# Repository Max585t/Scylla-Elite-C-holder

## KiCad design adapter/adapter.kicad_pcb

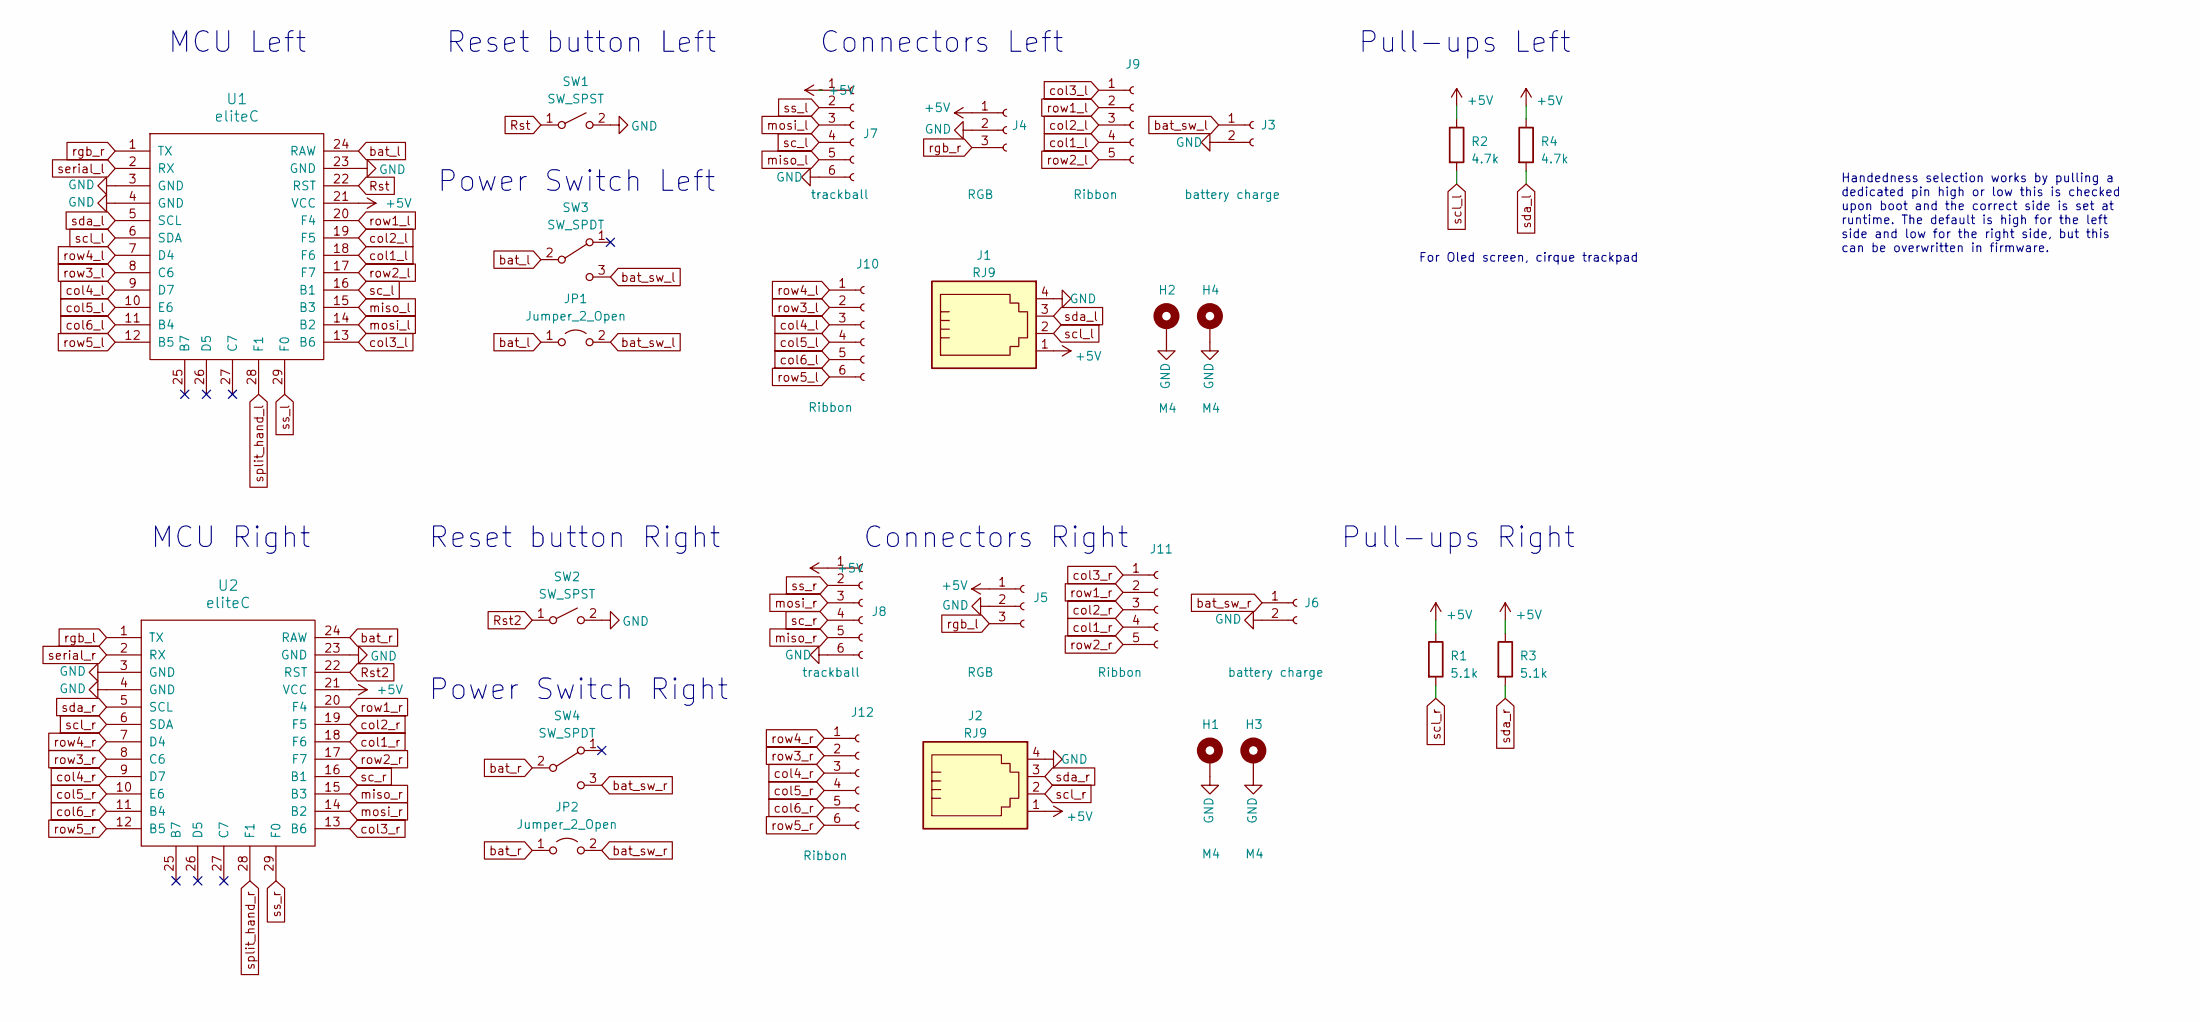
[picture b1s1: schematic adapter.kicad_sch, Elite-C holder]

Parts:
H1, H2, H3, H4: M4; MountingHole_4mm_Pad_thin
J1, J2: RJ9; MOLEX_0955012401
J3, J6: battery charge; PinHeader_1x02_P2.54mm_Vertical
J4, J5: RGB; header1x03
J7, J8: trackball; 6_PinHeader
J9, J11: Ribbon; 5_PinHeader
J10, J12: Ribbon; 6_PinHeader
JP1, JP2: Jumper_2_Open; power_switch_jumper
R1, R3: 5.1k; R_1206_handsolder; JLCPCB BOM 1
R2, R4: 4.7k; R_1206_handsolder; JLCPCB BOM 1
SW1, SW2: SW_SPST; PushSwitch
SW3, SW4: SW_SPDT; SW_SPDT+H-MSK12C01_hor(7pin_SMD)
U1, U2: eliteC; Elite-C

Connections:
+5V: J1.1, J2.1, J4.1, J5.1, J7.1, J8.1, R1.1, R2.1, R3.1, R4.1, U1.21 (VCC), U2.21 (VCC)
GND: H1.1, H2.1, H3.1, H4.1, J1.4, J2.4, J3.2, J4.2, J5.2, J6.2, J7.6, J8.6, SW1.2 (B), SW2.2 (B), U1.3 (GND), U1.4 (GND), U1.23 (GND), U2.3 (GND), U2.4 (GND), U2.23 (GND)
Rst: SW1.1 (A), U1.22 (RST)
Rst2: SW2.1 (A), U2.22 (RST)
bat_l: JP1.1 (A), SW3.2 (B), U1.24 (RAW)
bat_r: JP2.1 (A), SW4.2 (B), U2.24 (RAW)
bat_sw_l: J3.1, JP1.2 (B), SW3.3 (C)
bat_sw_r: J6.1, JP2.2 (B), SW4.3 (C)
col1_l: J9.4, U1.18 (F6)
col1_r: J11.4, U2.18 (F6)
col2_l: J9.3, U1.19 (F5)
col2_r: J11.3, U2.19 (F5)
col3_l: J9.1, U1.13 (B6)
col3_r: J11.1, U2.13 (B6)
col4_l: J10.3, U1.9 (D7)
col4_r: J12.3, U2.9 (D7)
col5_l: J10.4, U1.10 (E6)
col5_r: J12.4, U2.10 (E6)
col6_l: J10.5, U1.11 (B4)
col6_r: J12.5, U2.11 (B4)
miso_l: J7.5, U1.15 (B3)
miso_r: J8.5, U2.15 (B3)
mosi_l: J7.3, U1.14 (B2)
mosi_r: J8.3, U2.14 (B2)
rgb_l: J5.3, U2.1 (TX)
rgb_r: J4.3, U1.1 (TX)
row1_l: J9.2, U1.20 (F4)
row1_r: J11.2, U2.20 (F4)
row2_l: J9.5, U1.17 (F7)
row2_r: J11.5, U2.17 (F7)
row3_l: J10.2, U1.8 (C6)
row3_r: J12.2, U2.8 (C6)
row4_l: J10.1, U1.7 (D4)
row4_r: J12.1, U2.7 (D4)
row5_l: J10.6, U1.12 (B5)
row5_r: J12.6, U2.12 (B5)
sc_l: J7.4, U1.16 (B1)
sc_r: J8.4, U2.16 (B1)
scl_l: J1.2, R2.2, U1.6 (SDA)
scl_r: J2.2, R1.2, U2.6 (SDA)
sda_l: J1.3, R4.2, U1.5 (SCL)
sda_r: J2.3, R3.2, U2.5 (SCL)
serial_l: U1.2 (RX)
serial_r: U2.2 (RX)
split_hand_l: U1.28 (F1)
split_hand_r: U2.28 (F1)
ss_l: J7.2, U1.29 (F0)
ss_r: J8.2, U2.29 (F0)

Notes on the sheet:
Power Switch Right
Reset button Left
For Oled screen, cirque trackpad
Power Switch Left
Connectors Left
Pull-ups Right
Reset button Right
Handedness selection works by pulling a dedicated pin high or low this is checked upon boot and the correct side is set at runtime. The default is high for the left side and low for the right side, but this can be overwritten in firmware.
MCU Left
MCU Right
Pull-ups Left
Connectors Right

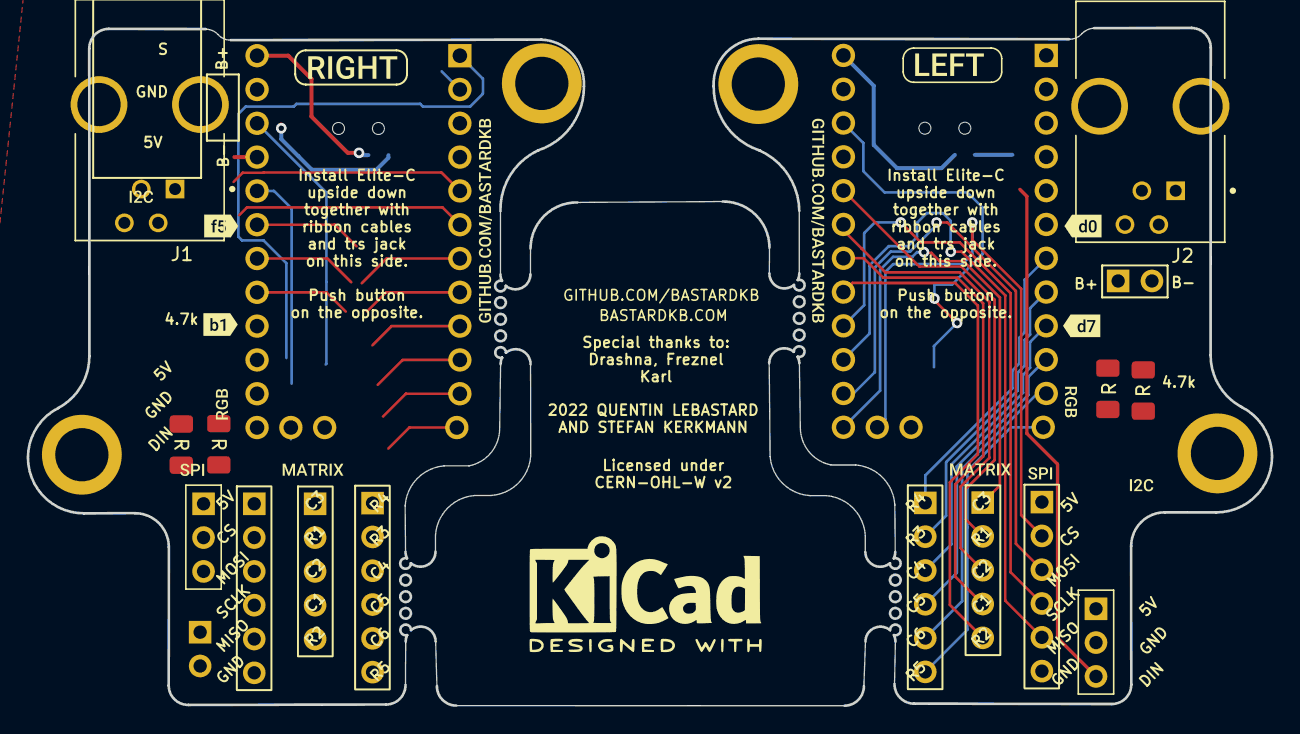
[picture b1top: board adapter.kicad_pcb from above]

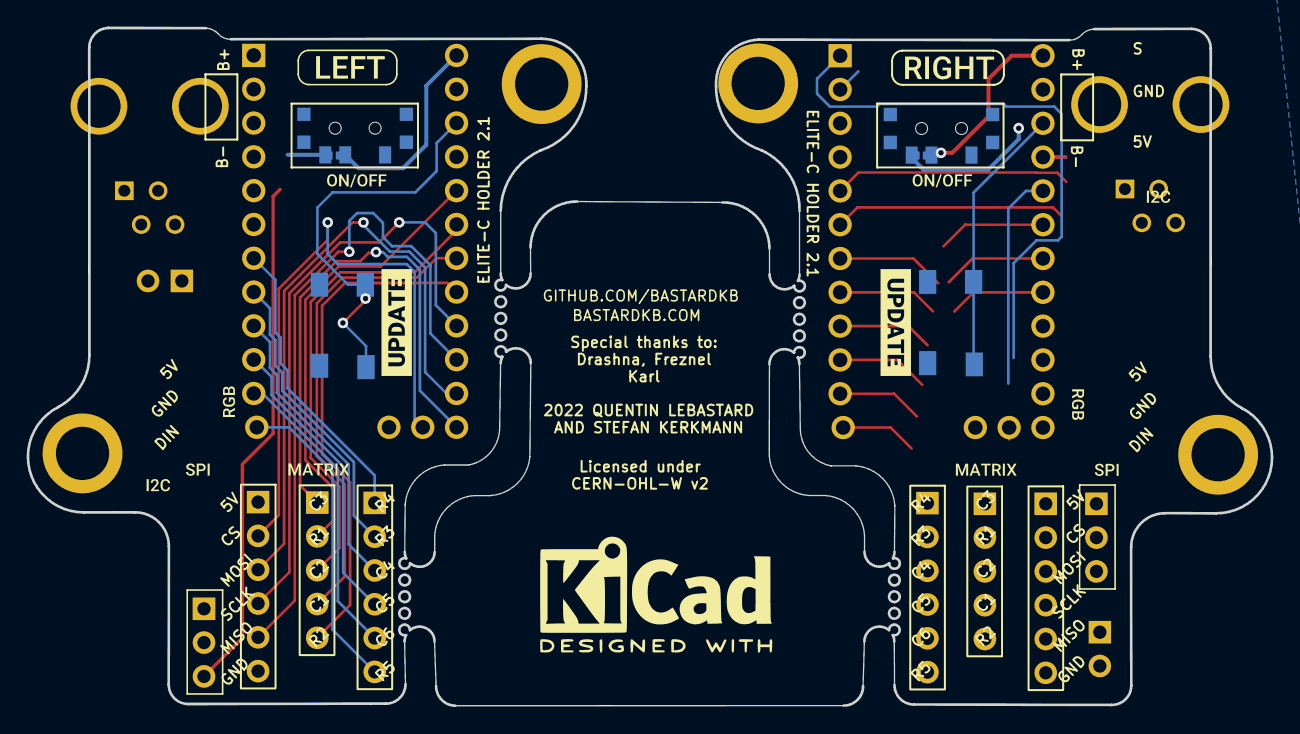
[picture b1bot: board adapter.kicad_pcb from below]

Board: 2 copper layers, 93.5 x 50.9 mm, 58 parts (22 on the bottom side), 44 nets.

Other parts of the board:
kibuzzard-61F01A92, kibuzzard-61F01A92#2: G***; kibuzzard-61F01A92
kibuzzard-61F01B61, kibuzzard-61F01B61#2: G***; kibuzzard-61F01B61
kibuzzard-61F01C84, kibuzzard-61F01C84#2: G***; kibuzzard-61F01C84
kibuzzard-61F019CB, kibuzzard-61F019CB#2, kibuzzard-61F019CB#3, kibuzzard-61F019CB#4: G***; kibuzzard-61F019CB
kibuzzard-61F01940, kibuzzard-61F01940#2, kibuzzard-61F01940#3, kibuzzard-61F01940#4: G***; kibuzzard-61F01940
kibuzzard-61F01957, kibuzzard-61F01957#2, kibuzzard-61F01957#3, kibuzzard-61F01957#4: G***; kibuzzard-61F01957
kibuzzard-620B8D91, kibuzzard-620B8D91#2, kibuzzard-620B8D91#3, kibuzzard-620B8D91#4: G***; kibuzzard-620B8D91
kibuzzard-620B8593, kibuzzard-620B8593#2: G***; kibuzzard-620B8593
kibuzzard-6208EDFE: G***; kibuzzard-6208EDFE
kibuzzard-6208EE22: G***; kibuzzard-6208EE22
kibuzzard-6208EFFE, kibuzzard-6208EFFE#2: G***; kibuzzard-6208EFFE
kibuzzard-62093EDE: G***; kibuzzard-62093EDE
kibuzzard-62094D1C: G***; kibuzzard-62094D1C

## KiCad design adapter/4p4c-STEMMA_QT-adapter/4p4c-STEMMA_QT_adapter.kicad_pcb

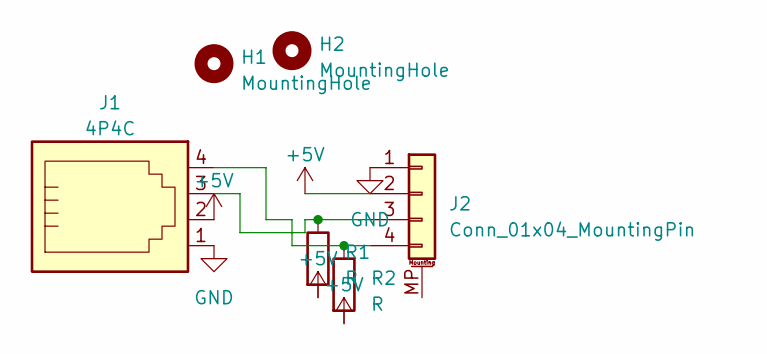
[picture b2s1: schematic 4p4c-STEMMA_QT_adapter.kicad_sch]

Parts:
H1, H2: MountingHole; MountingHole_2.2mm_M2_ISO14580
J1: 4P4C; MOLEX_0955012401
J2: Conn_01x04_MountingPin; JST_SH_BM04B-SRSS-TB_1x04-1MP_P1.00mm_Vertical
R1, R2: R; R_0805_2012Metric_Pad1.20x1.40mm_HandSolder

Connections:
+5V: J1.2, J2.2, R1.2, R2.2
GND: J1.1, J2.1
unnamed: J1.3, J2.3, R1.1
unnamed: J1.4, J2.4, R2.1

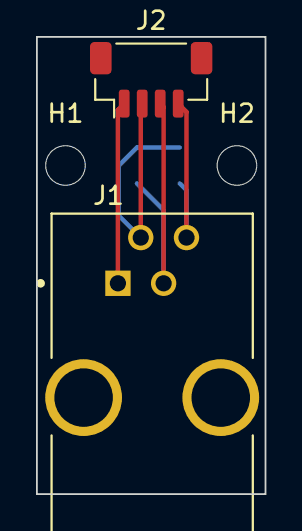
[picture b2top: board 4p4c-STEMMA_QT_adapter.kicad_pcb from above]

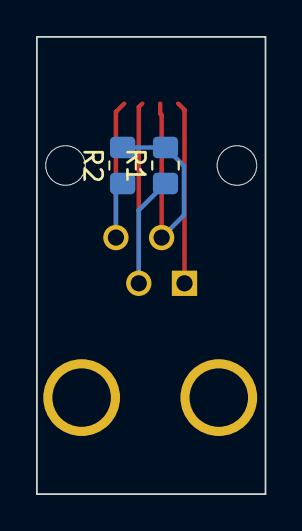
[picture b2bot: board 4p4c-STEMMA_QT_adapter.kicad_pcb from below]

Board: 2 copper layers, 12.7 x 25.4 mm, 6 parts (2 on the bottom side), 4 nets.

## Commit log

2023-11-21 initial work on rj9 mod
2023-11-22 initial work
2024-02-17 work done

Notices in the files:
adapter/adapter.kicad_pcb:
Licensed under
CERN-OHL-W v2
adapter/adapter.kicad_sch:
Licensed under CERN-OHL-W v2
